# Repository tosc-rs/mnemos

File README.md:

MnemOS ([`mnɛːmos`][name]) is a hobby-grade, experimental operating system for
[small computers][d1] (and [bigger ones, too][x86]). The MnemOS kernel and
userspace use a design based on asynchronous message passing, inspired by
[Erlang] and [microkernels], although MnemOS is not a true microkernel.

This repository contains the [cross-platform core of the MnemOS kernel][kernel],
which is implemented as a Rust library crate, [platform-specific
implementation][platforms] for supported hardware and simulator targets,
[development tools][tools] for working on MnemOS, and reusable libraries which
the kernel, tools, and platform implementations depend on.

[name]: https://mnemos.dev/mnemosprojectoverview/book/#where-does-the-name-come-fromhow-do-i-pronounce-it
[d1]: https://github.com/tosc-rs/mnemos/tree/main/platforms/allwinner-d1
[x86]: https://github.com/tosc-rs/mnemos/tree/main/platforms/x86_64
[Erlang]: https://en.wikipedia.org/wiki/Erlang_(programming_language)#Processes
[microkernels]: https://en.wikipedia.org/wiki/Microkernel
[kernel]: https://mnemos.dev/doc/kernel/
[platforms]: https://github.com/tosc-rs/mnemos/tree/main/platforms
[tools]: https://github.com/tosc-rs/mnemos/tree/main/tools

## Folder Layout

The project layout contains the following folders:

* [`assets/`] - images and files used for READMEs and other documentation
* [`book/`] - This is the source of "the mnemOS book"
* [`hardware/`] - Hardware designs for MnemOS systems, including CAD files and documentation
* [`source/`] - This folder contains the source code of the cross-platform kernel, userspace, and related libraries
* [`platforms/`] - This folder contains code specific to each targeted hardware and simulation platform
* [`rfcs/`] - MnemOS design RFCs
* [`tools/`] - This folder contains desktop tools used for working with MnemOS

[`assets/`]: ./assets/
[`book/`]: ./book/
[`hardware/`]: ./hardware/
[`source/`]: ./source/
[`platforms/`]: ./platforms/
[`tools/`]: ./tools/
[`rfcs/`]: ./rfcs/

## Getting Started

Currently, the primary supported hardware platform for MnemOS is the
Allwinner D1, a RISC-V system-on-chip (SOC). Instructions for running MnemOS on
D1 single-board computer can be found in [`platforms/allwinner-d1/README.md`].

If you don't have access to a supported D1 board, or want a quicker development
workflow for testing cross-platform changes, MnemOS also has a software
simulator, called [Melpomene]. Melpomene runs as a userspace application binary on
a development machine, and runs the MnemOS kernel with simulated hardware.
Melpomene can be run using the `just melpomene` [`just` recipe], or using
`cargo run --bin melpomene`.

[Pomelo] is a web-based simulator, which runs the MnemOS kernel in the browser
using WebAssembly. A hosted version of Pomelo can be found at
[https://web.versteht.es/mlem/][mlem].

> [!NOTE]
>
> Some [`just` recipe]s in the Justfile have additional build-time dependencies
> which must be installed on the user's system in order to run those recipes.
>
> In order to automate installing (most of) these dependencies, the
> [`manganese`] tool provides a wrapper for `just` recipes that depends on all
> Rust build dependencies from `crates.io` as normal cargo deps. To run a `just`
> recipe using `manganese`, run:
>
> ```bash
> cargo mn $RECIPE
> ```
>
> rather than
>
> ```bash
> just $RECIPE
> ```
>
> where `$RECIPE` is the name of the desired `just` recipe.

[`platforms/allwinner-d1/README.md`]: ./platforms/allwinner-d1/README.md
[Melpomene]: ./platforms/melpomene
[Pomelo]: https://github.com/tosc-rs/mnemos/tree/main/platforms/pomelo
[mlem]: https://web.versteht.es/mlem/
[`just` recipe]: ./justfile
[`manganese`]: ./tools/manganese/

## Learn More

### Development and API Docs

`rustdoc` output for the current `main` branch can be built locally with `cargo doc --open`.

- [the MnemOS book][book], a high-level discussion of MnemOS' design
- [hosted `main` branch API documentation][rustdoc] for the kernel and other
  MnemOS crates
- [a series of automatically-generated weekly updates][updates], which track
  MnemOS implementation progress over time

[book]: https://mnemos.dev/mnemosprojectoverview/book/
[rustdoc]: https://mnemos.dev/doc/kernel/
[updates]: https://mnemos.dev/mnemosprojectoverview/changelog/

### Development Blogs

We've written a series of development blogs following the story of MnemOS'
implementation. You can find them here:

- [MnemOS Moment 1][moment-1], by James Munns (2023-06-02)
- [MnemOS Moment 2: Search for a Shell][moment-2], by James Munns (2023-07-10)

[moment-1]: https://onevariable.com/blog/mnemos-moment-1/
[moment-2]: https://onevariable.com/blog/mnemos-moment-2/

## Getting Involved

Join us on Matrix: [#mnemos-dev:beeper.com](https://matrix.to/#/#mnemos-dev:beeper.com)

### License

[MIT] + [Apache 2.0].

[MIT]: https://github.com/tosc-rs/mnemos/blob/main/LICENSE-MIT
[Apache 2.0]: https://github.com/tosc-rs/mnemos/blob/main/LICENSE-APACHE

### Code of Conduct

The MnemOS project follows the [Contributor Covenant Code of Conduct](./code_of_conduct.md).

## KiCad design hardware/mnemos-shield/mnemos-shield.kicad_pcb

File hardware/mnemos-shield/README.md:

# Mnemos Shield

This is a basic breakout board for the beepy hardware, to overcome the fact that the MQ-Pro PTH are too small for the pogo pins used by the beepy board.

This board contains three 40-pin headers all connected in parallel with each other. All holes are 1.0mm inner diameter, which seems to work well on the pogo pins.

## Usage Warning

At the moment, it's not a *great* idea to power a beepy+MQ-Pro at the same time.

It's recommended (if you build one of these boards) to either:

* Don't connect the header pins for the MQ-Pro 5v0 rails
* Cut the traces on the shield

This will likely be fixed in a future revision. If you are planning to order boards from these design files, please drop by [#mnemos-dev:beeper.com](https://matrix.to/#/#mnemos-dev:beeper.com) so we can help you out!

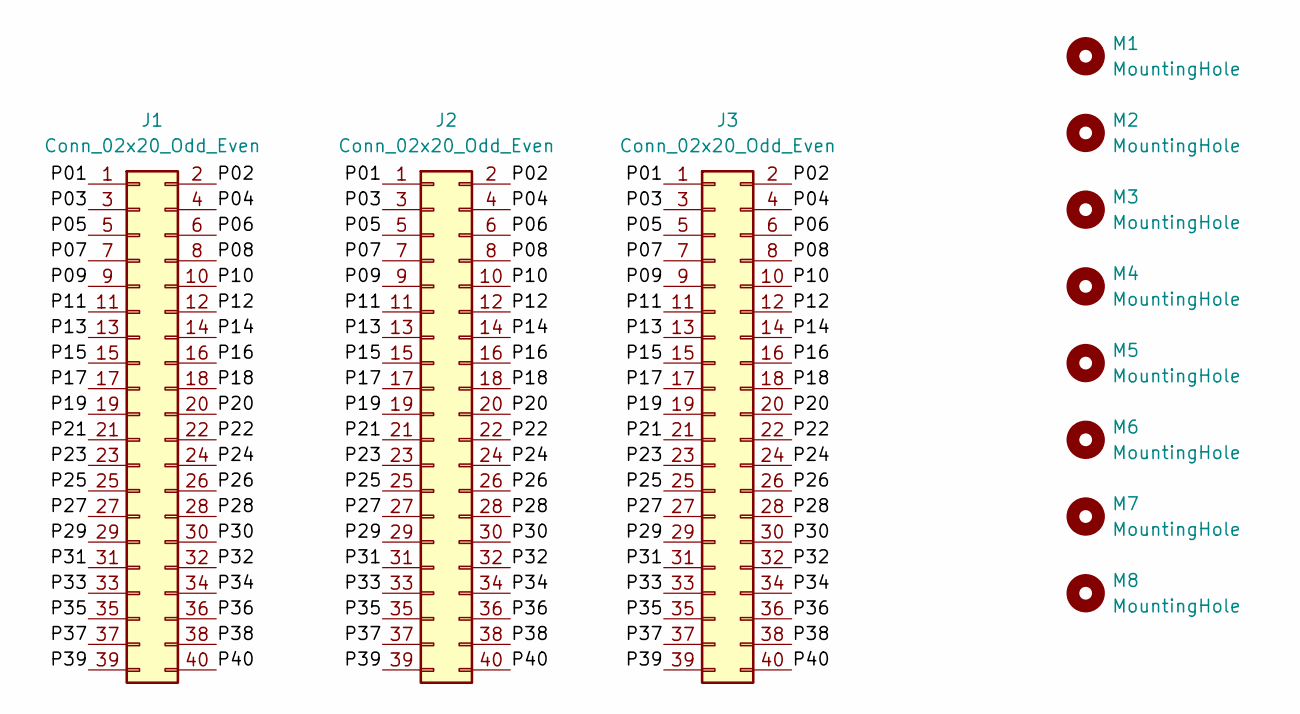
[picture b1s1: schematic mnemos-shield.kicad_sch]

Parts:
J1, J2, J3: Conn_02x20_Odd_Even; PinHeader_2x20_P2.54mm_Vertical
M1, M2, M3, M4, M5, M6, M7, M8: MountingHole; MountingHole_2.7mm_M2.5

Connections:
/P01: J1.1, J2.1, J3.1
/P02: J1.2, J2.2, J3.2
/P03: J1.3, J2.3, J3.3
/P04: J1.4, J2.4, J3.4
/P05: J1.5, J2.5, J3.5
/P06: J1.6, J2.6, J3.6
/P07: J1.7, J2.7, J3.7
/P08: J1.8, J2.8, J3.8
/P09: J1.9, J2.9, J3.9
/P10: J1.10, J2.10, J3.10
/P11: J1.11, J2.11, J3.11
/P12: J1.12, J2.12, J3.12
/P13: J1.13, J2.13, J3.13
/P14: J1.14, J2.14, J3.14
/P15: J1.15, J2.15, J3.15
/P16: J1.16, J2.16, J3.16
/P17: J1.17, J2.17, J3.17
/P18: J1.18, J2.18, J3.18
/P19: J1.19, J2.19, J3.19
/P20: J1.20, J2.20, J3.20
/P21: J1.21, J2.21, J3.21
/P22: J1.22, J2.22, J3.22
/P23: J1.23, J2.23, J3.23
/P24: J1.24, J2.24, J3.24
/P25: J1.25, J2.25, J3.25
/P26: J1.26, J2.26, J3.26
/P27: J1.27, J2.27, J3.27
/P28: J1.28, J2.28, J3.28
/P29: J1.29, J2.29, J3.29
/P30: J1.30, J2.30, J3.30
/P31: J1.31, J2.31, J3.31
/P32: J1.32, J2.32, J3.32
/P33: J1.33, J2.33, J3.33
/P34: J1.34, J2.34, J3.34
/P35: J1.35, J2.35, J3.35
/P36: J1.36, J2.36, J3.36
/P37: J1.37, J2.37, J3.37
/P38: J1.38, J2.38, J3.38
/P39: J1.39, J2.39, J3.39
/P40: J1.40, J2.40, J3.40

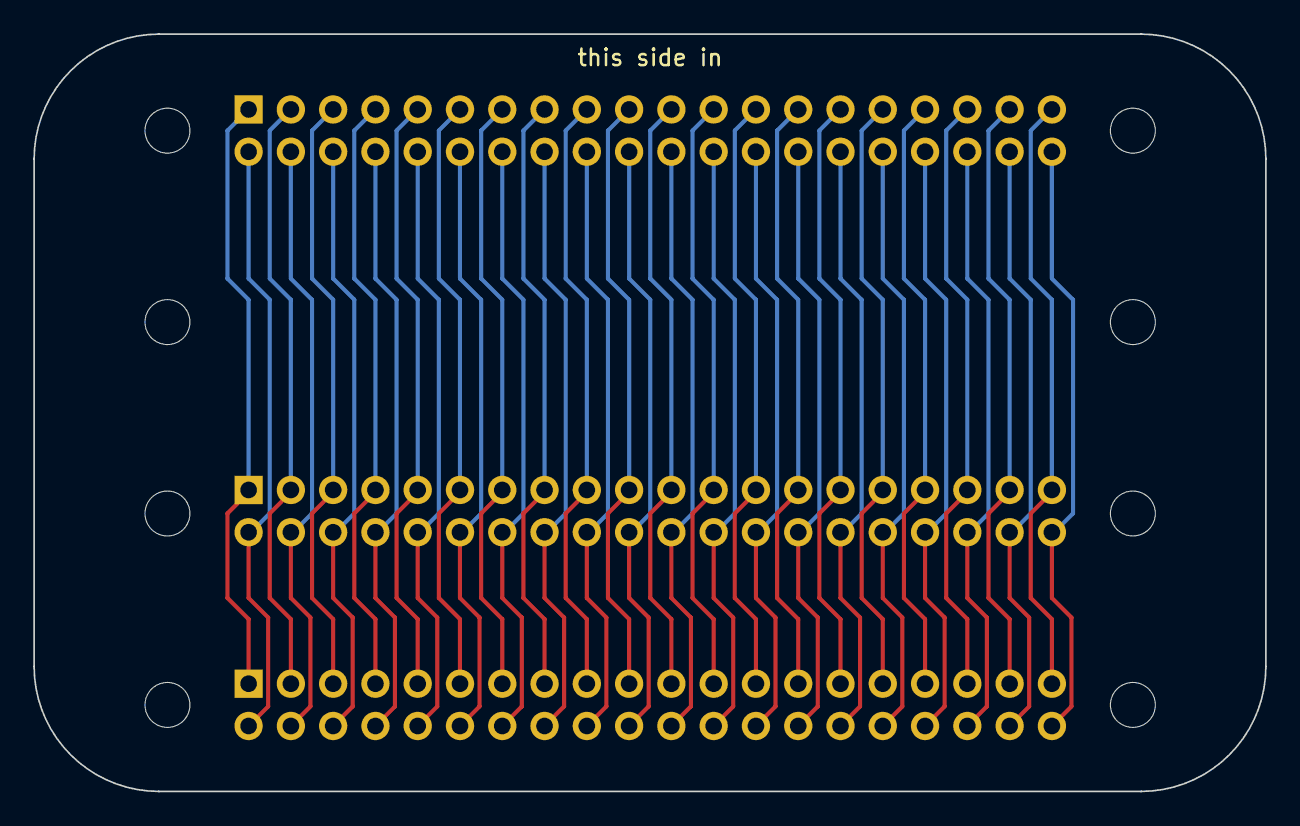
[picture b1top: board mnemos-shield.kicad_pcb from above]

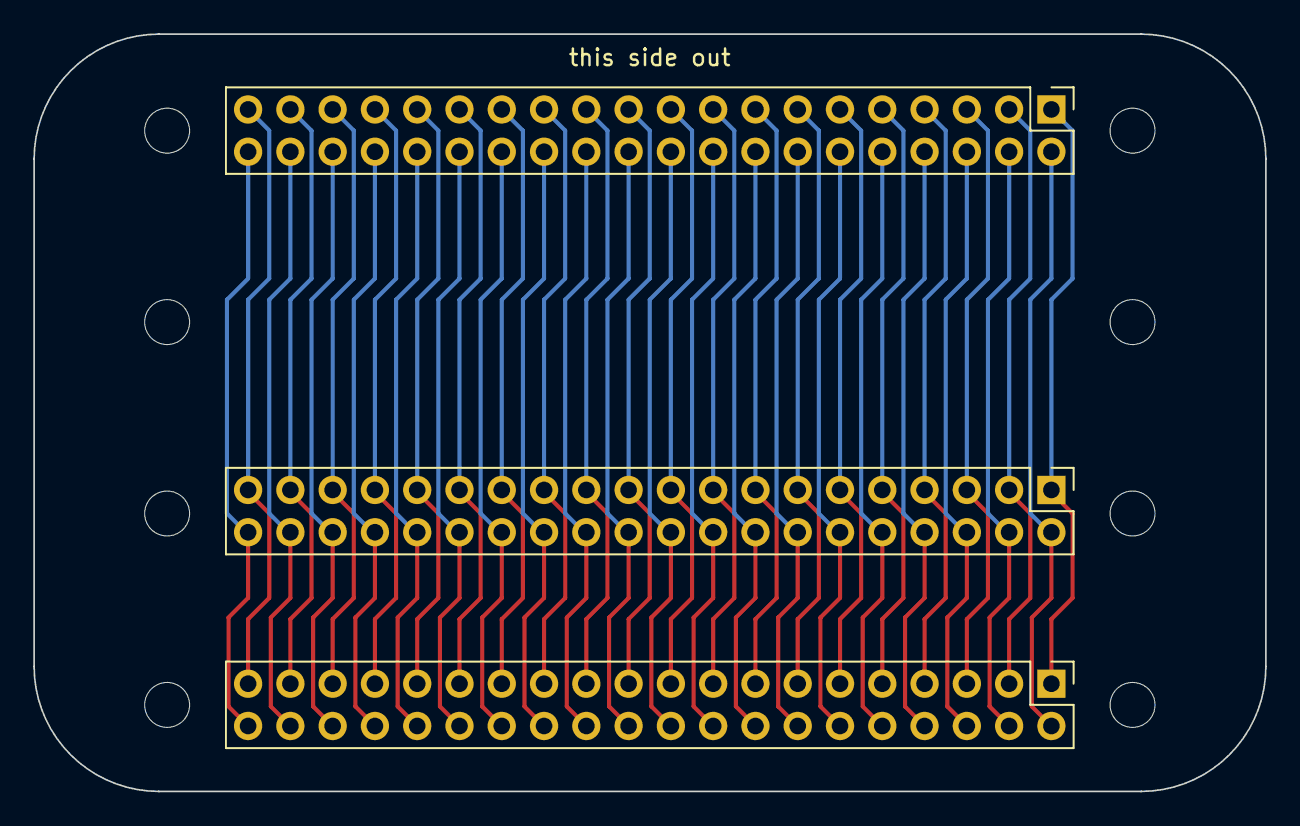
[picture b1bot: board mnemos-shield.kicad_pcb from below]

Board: 2 copper layers, 74.0 x 45.5 mm, 11 parts (3 on the bottom side), 40 nets.

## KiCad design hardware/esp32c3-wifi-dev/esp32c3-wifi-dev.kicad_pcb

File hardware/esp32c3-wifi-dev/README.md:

# esp32c3-wifi-dev

This is a breakout board for the [XIAO ESP32C3](https://wiki.seeedstudio.com/XIAO_ESP32C3_Getting_Started/) and the [XIAO RP2040](https://wiki.seeedstudio.com/XIAO-RP2040/).

The intent is to use these boards to implement a wifi modem firmware on the ESP32C3, and to speak to it using the RP2040 as a USB-to-UART+SPI adapter.

The initial plan is to implement a melpo service that acts as a SPI port, but tunnels the communication via USB to the RP2040, similar to (or perhaps exactly like) [`pretty-hal-machine`](https://github.com/jamesmunns/pretty-hal-machine).

```
.---------.           .---------.
|         +<-- SPI -->+         |
| RP2040  |           | ESP32C3 |
|         +<- UART -->+         |
'---USB---'           '---USB---'
     ^                     ^
     |                     |
     '-------> HUB <-------'
                ^
                |
                v
           .---USB---.
           +         |
           |  Melpo  |
           +   (PC)  |
           '---------'
```

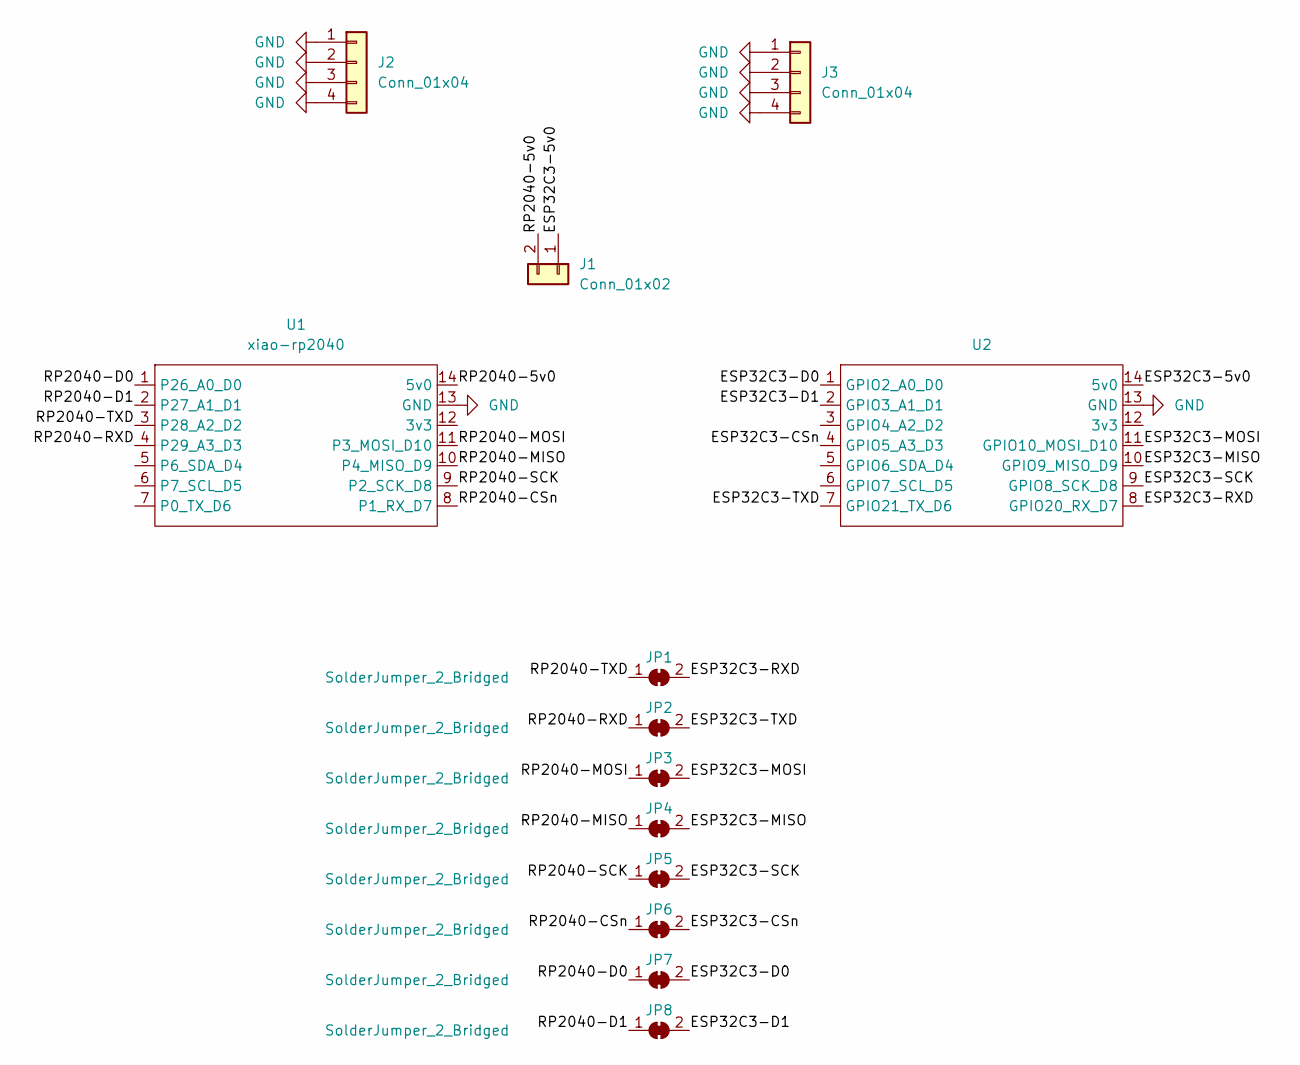
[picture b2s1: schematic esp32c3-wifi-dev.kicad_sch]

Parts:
J1: Conn_01x02; PinHeader_1x02_P2.54mm_Vertical
J2, J3: Conn_01x04; brick-1x4
JP1, JP2, JP3, JP4, JP5, JP6, JP7, JP8: SolderJumper_2_Bridged; SolderJumper-2_P1.3mm_Bridged_RoundedPad1.0x1.5mm
U1: xiao-rp2040; XIAO-Generic-Hybrid-14P-2.54-21X17.8MM
U2: XIAO-Generic-Hybrid-14P-2.54-21X17.8MM

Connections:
/ESP32C3-5v0: J1.1, U2.14 (5v0)
/ESP32C3-CSn: JP6.2 (B), U2.4 (GPIO5_A3_D3)
/ESP32C3-D0: JP7.2 (B), U2.1 (GPIO2_A0_D0)
/ESP32C3-D1: JP8.2 (B), U2.2 (GPIO3_A1_D1)
/ESP32C3-MISO: JP4.2 (B), U2.10 (GPIO9_MISO_D9)
/ESP32C3-MOSI: JP3.2 (B), U2.11 (GPIO10_MOSI_D10)
/ESP32C3-RXD: JP1.2 (B), U2.8 (GPIO20_RX_D7)
/ESP32C3-SCK: JP5.2 (B), U2.9 (GPIO8_SCK_D8)
/ESP32C3-TXD: JP2.2 (B), U2.7 (GPIO21_TX_D6)
/RP2040-5v0: J1.2, U1.14 (5v0)
/RP2040-CSn: JP6.1 (A), U1.8 (P1_RX_D7)
/RP2040-D0: JP7.1 (A), U1.1 (P26_A0_D0)
/RP2040-D1: JP8.1 (A), U1.2 (P27_A1_D1)
/RP2040-MISO: JP4.1 (A), U1.10 (P4_MISO_D9)
/RP2040-MOSI: JP3.1 (A), U1.11 (P3_MOSI_D10)
/RP2040-RXD: JP2.1 (A), U1.4 (P29_A3_D3)
/RP2040-SCK: JP5.1 (A), U1.9 (P2_SCK_D8)
/RP2040-TXD: JP1.1 (A), U1.3 (P28_A2_D2)
GND: J2.1, J2.2, J2.3, J2.4, J3.1, J3.2, J3.3, J3.4, U1.13 (GND), U2.13 (GND)

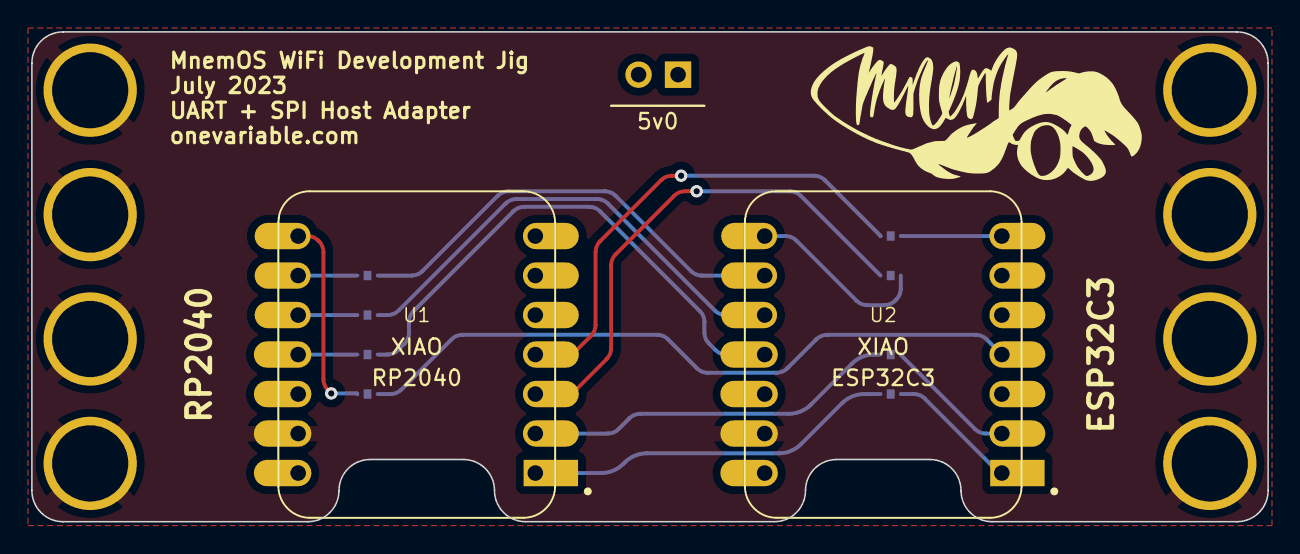
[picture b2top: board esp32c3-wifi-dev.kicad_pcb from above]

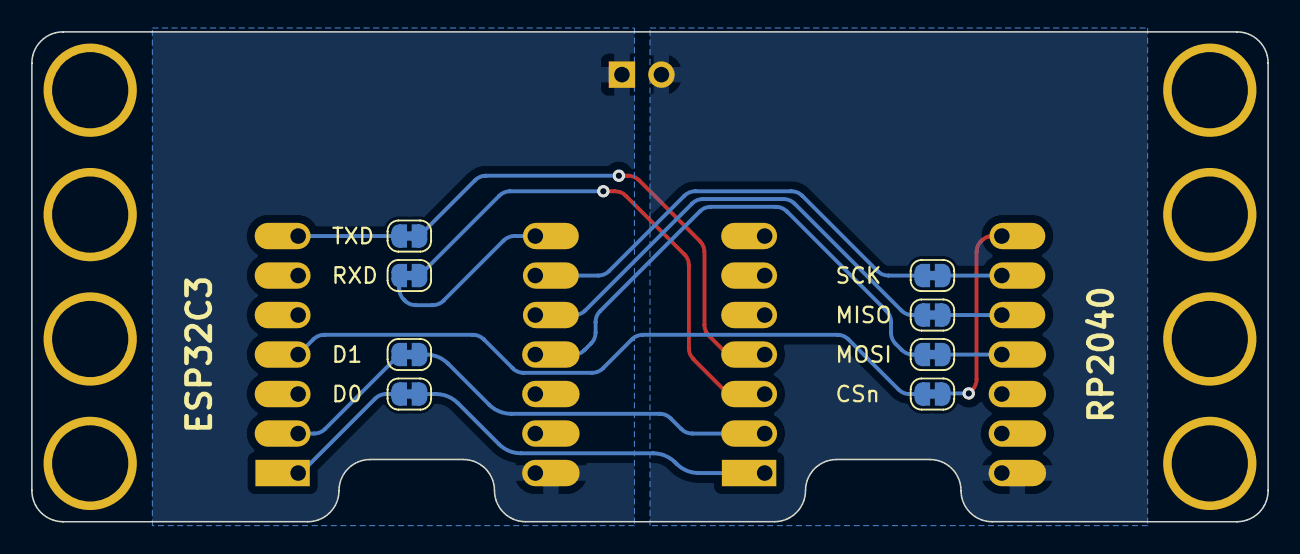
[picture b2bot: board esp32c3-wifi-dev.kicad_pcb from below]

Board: 2 copper layers, 79.5 x 31.5 mm, 13 parts (8 on the bottom side), 19 nets.

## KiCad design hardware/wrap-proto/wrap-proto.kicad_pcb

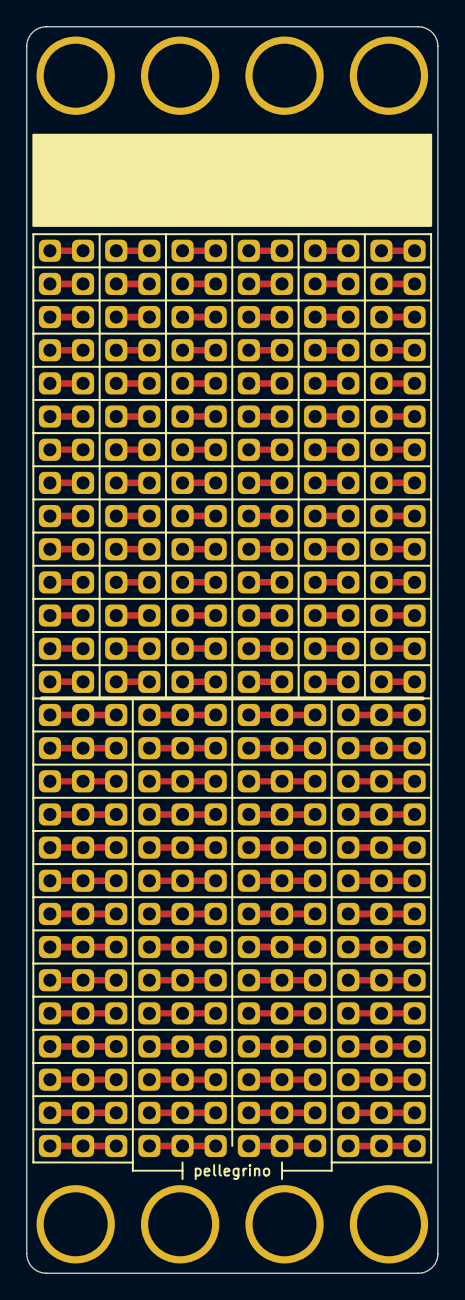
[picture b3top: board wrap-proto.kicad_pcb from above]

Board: 2 copper layers, 31.5 x 95.5 mm, 30 parts (0 on the bottom side), 140 nets.

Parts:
J1, J2, J3, J4, J5, J6, J7, J8, J9, J10, J11, J12, J13, J14, J15, J16, J17, J18, J19, J20, J21, J22, J23, J24, J25, J26, J27, J28: Conn_01x12; PinHeader_1x12_P2.54mm_Vertical
J29, J30: Conn_01x04; brick-1x4

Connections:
unnamed: J1.1, J1.2
unnamed: J1.3, J1.4
unnamed: J1.5, J1.6
unnamed: J1.7, J1.8
unnamed: J1.9, J1.10
unnamed: J1.11, J1.12
unnamed: J2.1, J2.2
unnamed: J2.3, J2.4
unnamed: J2.5, J2.6
unnamed: J2.7, J2.8
unnamed: J2.9, J2.10
unnamed: J2.11, J2.12
unnamed: J3.1, J3.2
unnamed: J3.3, J3.4
unnamed: J3.5, J3.6
unnamed: J3.7, J3.8
unnamed: J3.9, J3.10
unnamed: J3.11, J3.12
unnamed: J4.1, J4.2
unnamed: J4.3, J4.4
unnamed: J4.5, J4.6
unnamed: J4.7, J4.8
unnamed: J4.9, J4.10
unnamed: J4.11, J4.12
unnamed: J5.1, J5.2
unnamed: J5.3, J5.4
unnamed: J5.5, J5.6
unnamed: J5.7, J5.8
unnamed: J5.9, J5.10
unnamed: J5.11, J5.12
unnamed: J6.1, J6.2
unnamed: J6.3, J6.4
unnamed: J6.5, J6.6
unnamed: J6.7, J6.8
unnamed: J6.9, J6.10
unnamed: J6.11, J6.12
unnamed: J7.1, J7.2
unnamed: J7.3, J7.4
unnamed: J7.5, J7.6
unnamed: J7.7, J7.8
unnamed: J7.9, J7.10
unnamed: J7.11, J7.12
unnamed: J8.1, J8.2
unnamed: J8.3, J8.4
unnamed: J8.5, J8.6
unnamed: J8.7, J8.8
unnamed: J8.9, J8.10
unnamed: J8.11, J8.12
unnamed: J9.1, J9.2
unnamed: J9.3, J9.4
unnamed: J9.5, J9.6
unnamed: J9.7, J9.8
unnamed: J9.9, J9.10
unnamed: J9.11, J9.12
unnamed: J10.1, J10.2
unnamed: J10.3, J10.4
unnamed: J10.5, J10.6
unnamed: J10.7, J10.8
unnamed: J10.9, J10.10
unnamed: J10.11, J10.12
unnamed: J11.1, J11.2
unnamed: J11.3, J11.4
unnamed: J11.5, J11.6
unnamed: J11.7, J11.8
unnamed: J11.9, J11.10
unnamed: J11.11, J11.12
unnamed: J12.1, J12.2
unnamed: J12.3, J12.4
unnamed: J12.5, J12.6
unnamed: J12.7, J12.8
unnamed: J12.9, J12.10
unnamed: J12.11, J12.12
unnamed: J13.1, J13.2
unnamed: J13.3, J13.4
unnamed: J13.5, J13.6
unnamed: J13.7, J13.8
unnamed: J13.9, J13.10
unnamed: J13.11, J13.12
unnamed: J14.1, J14.2
unnamed: J14.3, J14.4
unnamed: J14.5, J14.6
unnamed: J14.7, J14.8
unnamed: J14.9, J14.10
unnamed: J14.11, J14.12
unnamed: J15.1, J15.2, J15.3
unnamed: J15.4, J15.5, J15.6
unnamed: J15.7, J15.8, J15.9
unnamed: J15.10, J15.11, J15.12
unnamed: J16.1, J16.2, J16.3
unnamed: J16.4, J16.5, J16.6
unnamed: J16.7, J16.8, J16.9
unnamed: J16.10, J16.11, J16.12
unnamed: J17.1, J17.2, J17.3
unnamed: J17.4, J17.5, J17.6
unnamed: J17.7, J17.8, J17.9
unnamed: J17.10, J17.11, J17.12
unnamed: J18.1, J18.2, J18.3
unnamed: J18.4, J18.5, J18.6
unnamed: J18.7, J18.8, J18.9
unnamed: J18.10, J18.11, J18.12
unnamed: J19.1, J19.2, J19.3
unnamed: J19.4, J19.5, J19.6
unnamed: J19.7, J19.8, J19.9
unnamed: J19.10, J19.11, J19.12
unnamed: J20.1, J20.2, J20.3
unnamed: J20.4, J20.5, J20.6
unnamed: J20.7, J20.8, J20.9
unnamed: J20.10, J20.11, J20.12
unnamed: J21.1, J21.2, J21.3
unnamed: J21.4, J21.5, J21.6
unnamed: J21.7, J21.8, J21.9
unnamed: J21.10, J21.11, J21.12
unnamed: J22.1, J22.2, J22.3
unnamed: J22.4, J22.5, J22.6
unnamed: J22.7, J22.8, J22.9
unnamed: J22.10, J22.11, J22.12
unnamed: J23.1, J23.2, J23.3
unnamed: J23.4, J23.5, J23.6
unnamed: J23.7, J23.8, J23.9
unnamed: J23.10, J23.11, J23.12
unnamed: J24.1, J24.2, J24.3
unnamed: J24.4, J24.5, J24.6
unnamed: J24.7, J24.8, J24.9
unnamed: J24.10, J24.11, J24.12
unnamed: J25.1, J25.2, J25.3
unnamed: J25.4, J25.5, J25.6
unnamed: J25.7, J25.8, J25.9
unnamed: J25.10, J25.11, J25.12
unnamed: J26.1, J26.2, J26.3
unnamed: J26.4, J26.5, J26.6
unnamed: J26.7, J26.8, J26.9
unnamed: J26.10, J26.11, J26.12
unnamed: J27.1, J27.2, J27.3
unnamed: J27.4, J27.5, J27.6
unnamed: J27.7, J27.8, J27.9
unnamed: J27.10, J27.11, J27.12
unnamed: J28.1, J28.2, J28.3
unnamed: J28.4, J28.5, J28.6
unnamed: J28.7, J28.8, J28.9
unnamed: J28.10, J28.11, J28.12

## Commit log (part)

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2023-08-30 remove synthetic key events
2023-08-30 logs--
2023-08-30 force fast startup by enqueuing one irq
2023-08-30 add missing IRQs
2023-09-01 start updating platform svcs
2023-09-02 rename `Connection` to `Handshake`
    This lets us save the name `Connection` to represent the
    _established_ connection.
2023-09-02 must_use all the things
2023-09-02 docs and error type improvement
2023-09-03 fix comment
2023-09-03 feat(kernel): improve `registry` tracing (#266)
    The registry emits a bunch of `tracing` diagnostics, but they're not
    *that* helpful in most cases. In particular, when we get a service, we
    log its UUID, but this isn't super readable for someone consuming the
    logs --- you have to then take that UUID and look it up against the
    table of potential UUIDs to figure out which service was being looked
    up. Also, some of the errors introduced in #258 look pretty lousy in
2023-09-03 refac: use `bind` helpers to reduce boilerplate
2023-09-03 fix bad eq impl
2023-09-11 more docs fixy
2023-09-13 Split out per-target tomls
2023-09-14 fixup
2023-09-14 fix wrong non-toml skipping logic
2023-09-14 chore(ci): actually build bin targets on CI (#272)
    It turns out we weren't actually building binaries at all on CI, just
    running `cargo check` for them. This means that changes that only effect
    link-time behavior can break our build, and CI won't notice. For
    example, PR #271 accidentally ate the D1 linker script, so the actual
    binary build broke, and we didn't notice.
2023-09-15 Add that `mn` requires bindeps
    Without this installing errors with:
    ```rust
    error: failed to parse manifest at `mnemos/tools/manganese/Cargo.toml`
    Caused by:
    `artifact = …` requires `-Z bindeps` (cargo-binutils)
    ```
2023-09-16 as_data -> into_data
2023-09-16 fix(d1): put back missing `serial-trace` feature
    Looks like the feature flag was lost in #271, so the D1 binaries no
    longer emit traceproto output. I believe this happened when combining
    the `mnemos-d1` crate (which used to enable the feature) with the
    `mnemos-d1-core` crate (which didn't enable the feature).
    This commit puts it back. :)
2023-09-16 platform(d1): allocate DMA channels from DMAC
2023-09-17 feat(bitslab): add a 16-bit index allocator
    This introduces an atomic allocator for up to 16 unique indices. I need
    this for the DMAC allocator, which has 16 channels. But, we can also add
    bigger bitfields later for use in pools of up to 64 (or 128) objects.
    Probably these could be macro-generated later. Whatever.
2023-09-17 put public APIs first
2023-09-17 feat(bitslab): method name feedback + more utils
2023-09-17 test(abi): delete super broken `bbqueue_ipc` doctests
    These doctests reference APIs that don't exist in this module. I
    believe this probably happened due to @jamesmunns copying code from his
    upstream `bbqueue` crate, changing the APIs, and forgetting to update
    the doctests? Anyway, I just removed them.
2023-09-17 haha yay it works
2023-09-17 feature/dep pruning + fixy
2023-09-18 redo link address validation
2023-09-18 just use `build_raw` in drivers
2023-09-20 type `Configuration` less often
2023-09-20 move private types down
2023-09-20 feat(D1): add builders for DMAC descriptors (#284)
    Currently, the DMAC descriptor configuration fields are bit-packed every
    time a descriptor is constructed. However, the drivers which use DMA
    always construct descriptors with the same configuration bitfields --
    only the addresses and lengths change. We can make this more efficient
    by constructing the config field once and copying it into each new
    descriptor.
2023-09-21 feat(kernel): initialize tracing subscriber earlier (#288)
    This changes the `tracing` initialization so that the subscriber is
    registered as the default *without* waiting for SerMux to actually come
    up. This way, we can trace stuff that happens before the serial driver
    starts: anything we record gets buffered, and then is sent over serial once
    serial comes up. This lets us trace more of the boot process.
2023-09-21 feat(crowtty): nicer span enter/exit logs (#289)
    This commit changes the span enter/exit logs to be a bit more consistent
2023-09-22 feat(bitslab): add 8, 32, and 64-bit `IndexAlloc`s
    For completeness, it's nice to have all of these.
2023-10-04 fix wrong all_free behavior
2023-10-05 docs: actually add platforms to the book (#294)
2023-10-06 fix(x86_64): fix `TraceSubscriber` emitting enter instead of exit (#296)
    Currently, the `x86_64` `TraceSubscriber` incorrectly writes a duplicate
    `Enter` message to the serial port when a span is exited, instead of an
    `Exit` message. This commit fixes that.
    Fixes #290
2023-10-14 feat(bitslab): bitslabs participate in loom
2023-10-26 chore: update lockfile (#298)
2023-10-26 Create sdmmc kernel service, copied from i2c service
2023-10-26 Add smhc in `src/lib.rs`
2023-10-26 sdmmc: add *data* field to `Response::Short`
2023-10-26 sdmmc: implement more functions
    - `get_cid`
    - `get_rca`
    - `select`
    - `set_wide_bus`
2023-11-19 smhc: extract `reset_fifo` function
2023-11-19 smhc: fix some check + clippy lints
2023-11-20 sdmmc: map [u32;4] to u128 for card identification register
2023-11-21 smhc: update some doc comments
2023-11-28 pin to earlier nextest
2023-12-05 sdmmc: `Response::Long` contains u128
    + smhc: use transmute to convert [u32;4] to u128
2023-12-10 feat(d1): add smhc driver (#299)
    This PR adds support for SD card interaction on the Allwinner D1 platform.
    It is split in an `sdmmc` kernel service and a driver for the
    SD/MMC host controller peripheral.
    Currently only SD card support is implemented,
    but this should allow for adding MMC and SDIO support later.
    The interface between the kernel service and the driver aims to work on
2024-01-17 style: fix a pile of "dumb but fair" clippy lints
    basically all of these are related to doc comments in various ways. to
    which i generally say: "who cares?"
2024-01-21 refac(D1): move spin delay from `ccu` to `clint`
    This branch addresses a minor TODO in the `ccu` module, by moving the
    spin delay function from the `ccu` module into a function on the `Clint`
    type. Additionally, I've removed the `&self` receiver from
    `Clint::get_mtime`, since we don't actually use the `&self`. This lets
    us change `get_mtime` to a free function, and therefore remove the
    `unsafe` calls to `Clint::summon()` in a few places, so we can get rid
2024-01-21 rm feature flag
2024-04-09 chore: update to `mycelium-bitfield` v0.1.5 (#311)
    This rolls our Mycelium Git deps to
    hawkw/mycelium@13d0722429ef201f38e4ea47ea22d88f3f72c10e
2024-04-09 fix(d1): actually handle interrupt array sparsity
2024-04-10 chore(ci): don't manually install wasm toolchain (#315)
    This is already specified in the toolchain file, so it needn't be
    manually installed on CI.
2024-08-10 fix(scripts): confirm script should default to Y (#321)
    The `confirm` helper function used in our build scripts prints "[Y/n]",
    which suggests that "yes" is the default option. However, if you press
    enter, it just says "invalid input" and retries, which is not what it
    claims to do. This commit fixes that.
    For example, a test script like:
    ```bash
2024-08-10 cargo update
2024-08-10 fix bindep-related build failure
2024-08-10 add SPECIFIC rust-src component to clippy action
2024-08-10 experiment: remove forced-target and see what breaks
2024-08-10 justfile: fix _x86_pkg referring to bootloader instead of core
2024-08-10 use jq to filter and output final format
2024-08-11 ensure default cargo target dir
2024-08-11 shut up clippy
2024-08-13 try to debug CI borkage with more verbose env settings
2024-08-13 document running melpo under macos with homebrew-installed sdl2
2024-08-13 additional info re: D1 running/verifying successful install
2024-08-20 Fix invalid link to platforms in README
2024-08-29 docs: fix invalid link to platforms in README (#329)
2024-09-11 style: use core `ready`, `poll_fn`, and `pin!` (#331)
    Currently, we use the `future::ready` and `future::poll_fn` functions
    and the `pin_mut!` macro from the `futures` crate. The equivalent APIs
    in libcore have stabilized, so we can use them instead.
    Because we use a bunch of other stuff from `futures` --- in particular,
    `futures::select!` --- this doesn't allow us to reduce our dependency
    footprint by removing dependencies on `futures`. But, IMO, it feels like
2024-09-29 unshorten flags
2024-09-29 move to tools dir
2024-09-30 rustfmt
2024-10-02 verbose
2024-10-02 now with qemu log grabbing
2024-10-03 Specify how to create a `Registration` in its doc comment.
    As a brand new reader of the mnemos kernel docs, this was a bit difficult to discover. I started at `Registry::register`, and saw that it requires a `Registration`. But `Registration` has no construc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
2024-10-06 cleanup OVMF crap more nicely
2024-10-06 make verbose flag less confusing
2024-10-06 tools: extra goofy cargo-style logger tweaks (#340)
    I am the worst.
2024-10-08 tools: separate crowtty bin from libuv dep, fix CI (#342)
    The `crowtty` CLI requires `libuv` on Linux systems in order to interact
    with serial devices. This is why the x86_64 build is now failing on CI,
    since the bootimage builder depends on `crowtty` in order to run it on
    the QEMU virtual serial port, but building crowtty requires `libuv`.
    See:
    https://github.com/tosc-rs/mnemos/issues/341#issuecomment-2395519851
2024-12-27 tools: enable fancy miette errors in `crowtty` (#345)
    At some point (probably when `crowtty` was separated out into its own
    binary in #342), the `miette` dependency's `"fancy"` feature flag, which
    makes the debug print format for errors actually look nice and include
    cause chains, was eaten. This is a bummer, because having cause chains
    is important in order to understand the error message.
    This commit re-enables the `"fancy"` feature flag for `miette` in
2024-12-27 update everything
2024-12-27 pedantry
2024-12-27 do esp32
2024-12-27 implement timer 0 rollover
    This implements an ancient TODO about how we ought to handle 32-bit
    timer 0 rollovers. I also abstracted a bunch more of the timer 0
    configuration behind the timer module, so the rest of the kernel doesn't
    have to know about it.
